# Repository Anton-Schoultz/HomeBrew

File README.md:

# HomeBrew
My attempt at rolling-my-own reto 80's home computer.

Aiming for a 6502 (specifically R65C02) based system,
ideally with video output.

# Tools
Here I have collected the various tools that I needed.
<br>See the README.md in the tools folder for more info.

## EE Programmer
Used to program the EEPROM that I use, the PQ 52B33, which is an 8K rom. 
Programmed via an arduino circuit, using java code on the pc side.

## GAL Programmer
Used to program the GAL20V8s that I use (available and affordable here).
<br>Bassed on the Afterburner project by Bruce Abbott.
<br>I added some convenience batch jobs GAL_Write.bat and GAL_Read.bat.

## Logic Analyser
Here I made use of the excellent PulseView Program,
using a Raspberry Pi Pico as the data capture device.

## WinCUPL
This outdated program from ATMEL is used to compile the fuse info for
programming the GAL20V8 chips.

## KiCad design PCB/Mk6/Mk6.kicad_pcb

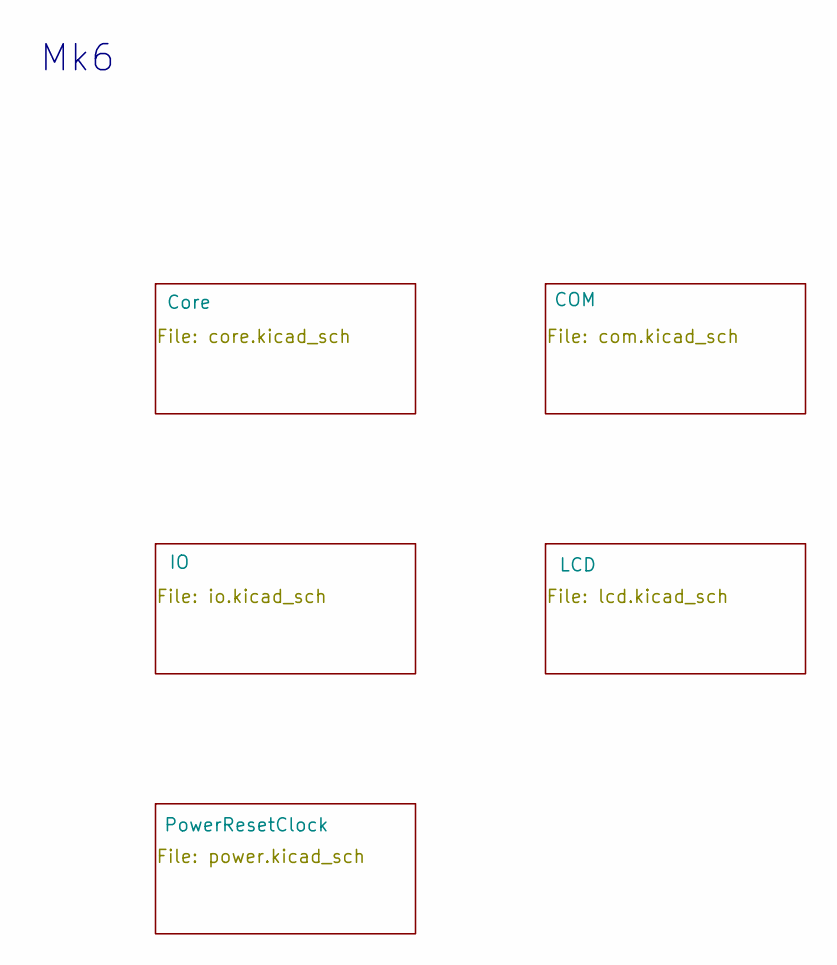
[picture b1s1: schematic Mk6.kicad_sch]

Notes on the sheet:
Mk6

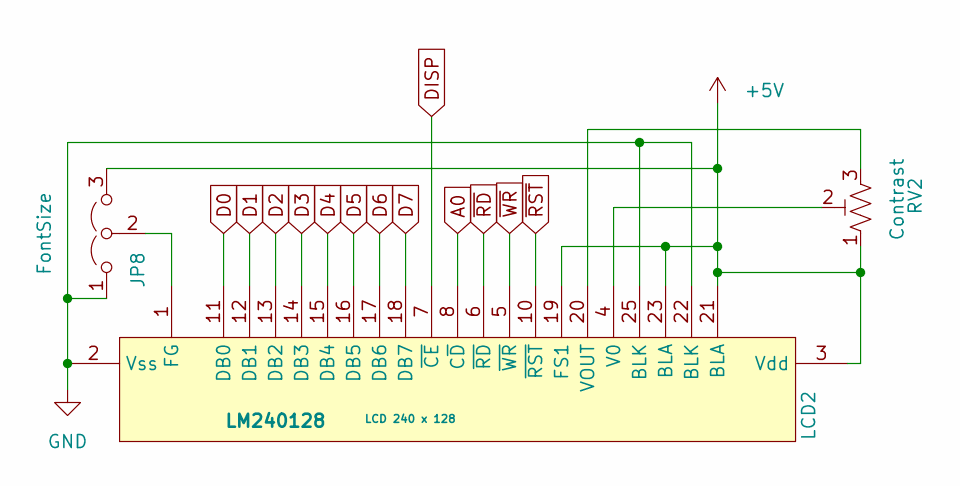
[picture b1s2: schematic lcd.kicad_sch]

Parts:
JP8: FontSize; PinHeader_1x03_P2.54mm_Vertical
LCD2: LM240128; LCD 240x128
RV2: Contrast; Potentiometer_Piher_PT-15-V15_Vertical

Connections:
+5V: JP8.3 (B), LCD2.3 (Vdd), LCD2.19 (FS1), LCD2.21 (BLA), LCD2.23 (BLA), RV2.1; also elsewhere on the board
A0: LCD2.8 (C~D); also elsewhere on the board
D0: LCD2.11 (DB0); also elsewhere on the board
D1: LCD2.12 (DB1); also elsewhere on the board
D2: LCD2.13 (DB2); also elsewhere on the board
D3: LCD2.14 (DB3); also elsewhere on the board
D4: LCD2.15 (DB4); also elsewhere on the board
D5: LCD2.16 (DB5); also elsewhere on the board
D6: LCD2.17 (DB6); also elsewhere on the board
D7: LCD2.18 (DB7); also elsewhere on the board
DISP: LCD2.7 (~CE); also elsewhere on the board
GND: JP8.1 (A), LCD2.2 (Vss), LCD2.22 (BLK), LCD2.25 (BLK); also elsewhere on the board
unnamed: JP8.2 (C), LCD2.1 (FG)
unnamed: LCD2.4 (V0), RV2.2
unnamed: LCD2.20 (VOUT), RV2.3
~RD: LCD2.6 (~RD); also elsewhere on the board
~RST: LCD2.10 (~RST); also elsewhere on the board
~WR: LCD2.5 (~WR); also elsewhere on the board

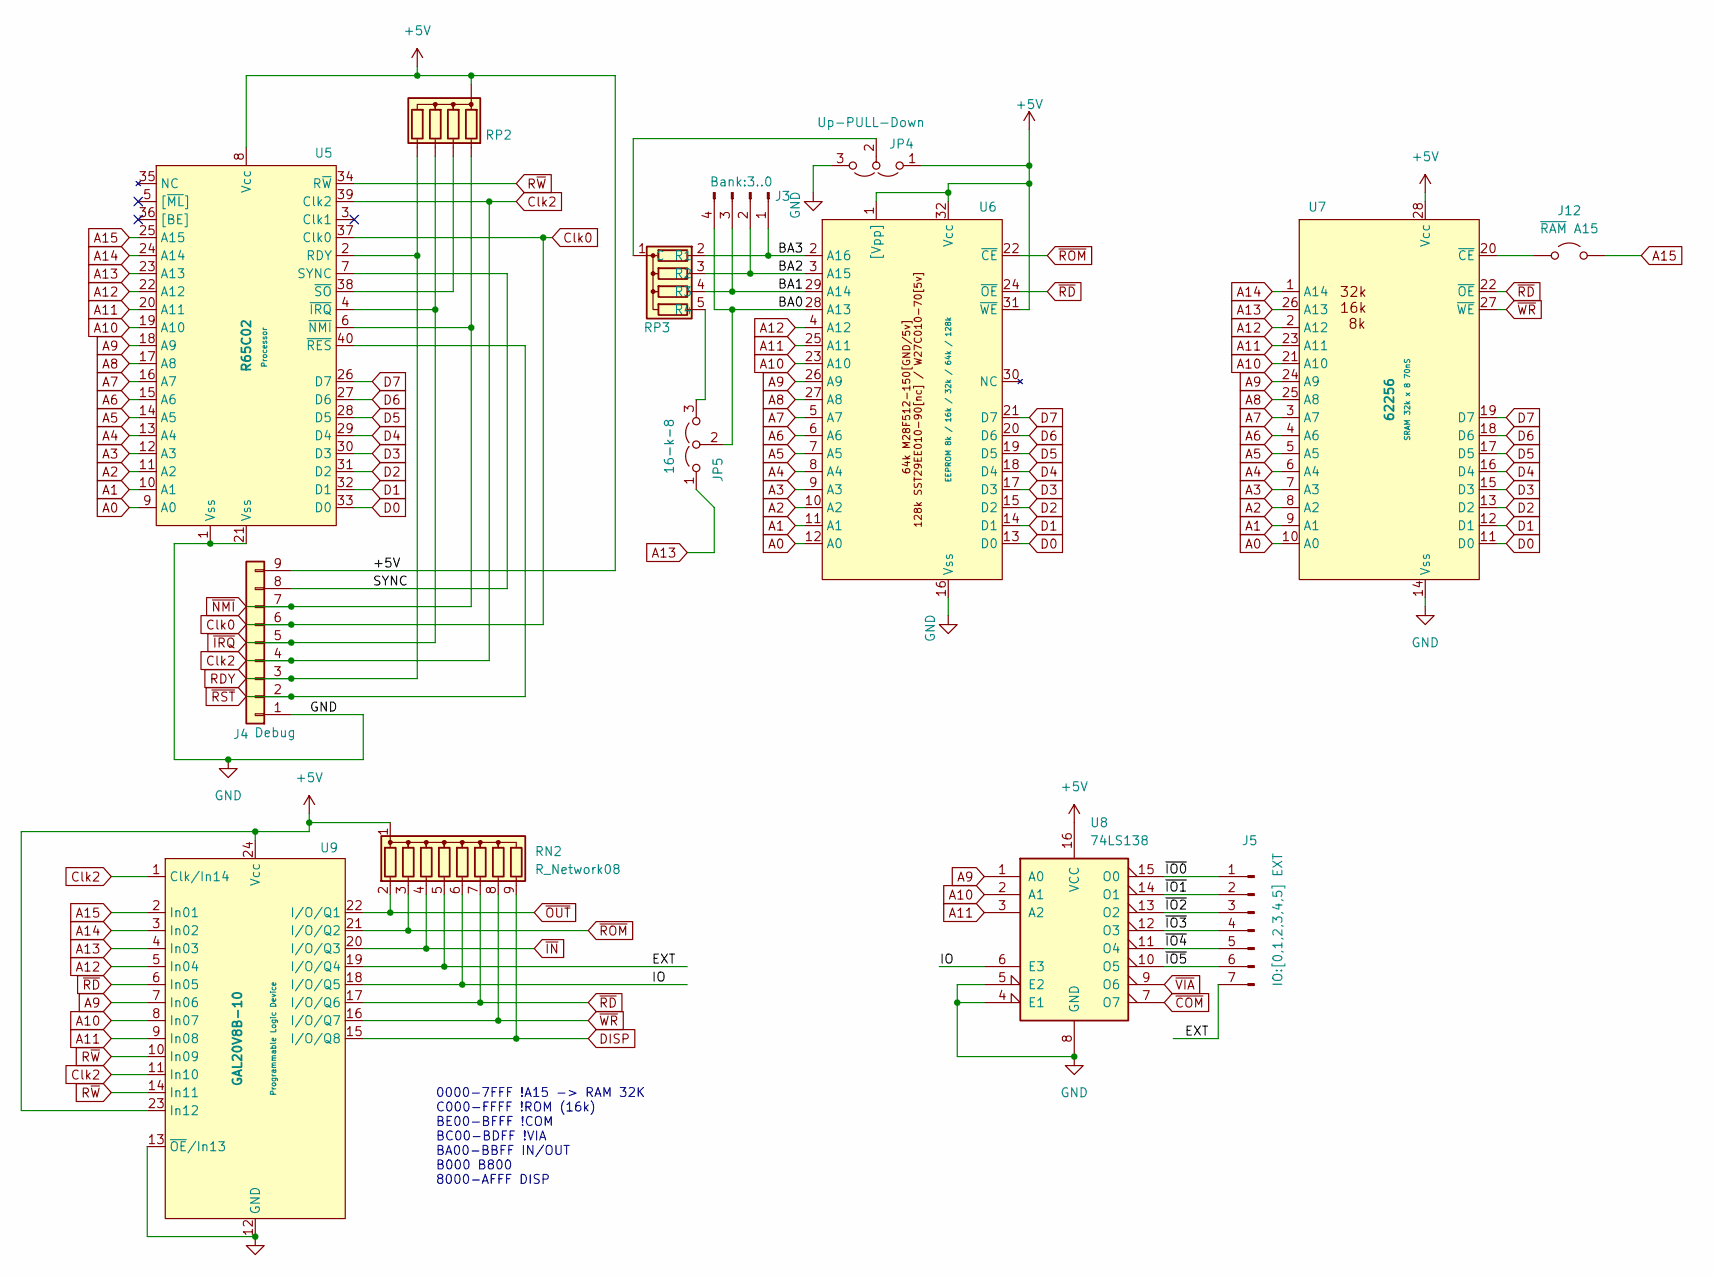
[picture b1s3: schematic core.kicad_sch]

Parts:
J3: Bank:3..0; PinHeader_1x04_P2.54mm_Vertical
J4: Debug; PinHeader_1x09_P2.54mm_Vertical
J5: IO:[0,1,2,3,4,5] EXT; PinSocket_1x07_P2.54mm_Vertical
J12: ~{RAM} A15; PinHeader_1x02_P2.54mm_Vertical
JP4: Up-PULL-Down; PinHeader_1x03_P2.54mm_Vertical
JP5: 16-k-8; PinHeader_1x03_P2.54mm_Vertical
RN2: R_Network08; R_Array_SIP9
RP2, RP3: R_Array_SIP5
U5: R65C02; DIP-40_W15.24mm_LongPads
U6: EEPROM; DIP_Socket-32_W11.9_W12.7_W15.24_W17.78_W18.5_3M_232-1285-0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
U7: 62256; DIP-28_W15.24mm_LongPads
U8: 74LS138; DIP-16_W7.62mm_LongPads
U9: GAL20V8B-10; DIP-24_W7.62mm_LongPads

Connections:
+5V: J4.9, JP4.1 (A), RN2.1 (common), RP2.1 (C), U5.8 (Vcc), U6.1 ([Vpp]), U6.31 (~WE), U6.32 (Vcc), U7.28 (Vcc), U8.16 (VCC), U9.23 (In12), U9.24 (Vcc); also elsewhere on the board
/Core/BA0: J3.4, JP5.2 (C), U6.28 (A13)
/Core/BA1: J3.3, RP3.4 (R3), U6.29 (A14)
/Core/BA2: J3.2, RP3.3 (R2), U6.3 (A15)
/Core/BA3: J3.1, RP3.2 (R1), U6.2 (A16)
/Core/EXT: J5.7, RN2.5 (R4), U9.19 (I/O/Q4)
/Core/IO: RN2.6 (R5), U8.6 (E3), U9.18 (I/O/Q5)
/Core/SYNC: J4.8, U5.7 (SYNC)
/Core/~IO0: J5.1, U8.15 (O0)
/Core/~IO1: J5.2, U8.14 (O1)
/Core/~IO2: J5.3, U8.13 (O2)
/Core/~IO3: J5.4, U8.12 (O3)
/Core/~IO4: J5.5, U8.11 (O4)
/Core/~IO5: J5.6, U8.10 (O5)
A0: U5.9 (A0), U6.12 (A0), U7.10 (A0); also elsewhere on the board
A1: U5.10 (A1), U6.11 (A1), U7.9 (A1); also elsewhere on the board
A2: U5.11 (A2), U6.10 (A2), U7.8 (A2); also elsewhere on the board
A3: U5.12 (A3), U6.9 (A3), U7.7 (A3); also elsewhere on the board
A4: U5.13 (A4), U6.8 (A4), U7.6 (A4); also elsewhere on the board
A5: U5.14 (A5), U6.7 (A5), U7.5 (A5); also elsewhere on the board
A6: U5.15 (A6), U6.6 (A6), U7.4 (A6); also elsewhere on the board
A7: U5.16 (A7), U6.5 (A7), U7.3 (A7); also elsewhere on the board
A8: U5.17 (A8), U6.27 (A8), U7.25 (A8); also elsewhere on the board
A9: U5.18 (A9), U6.26 (A9), U7.24 (A9), U8.1 (A0), U9.7 (In06); also elsewhere on the board
A10: U5.19 (A10), U6.23 (A10), U7.21 (A10), U8.2 (A1), U9.8 (In07); also elsewhere on the board
A11: U5.20 (A11), U6.25 (A11), U7.23 (A11), U8.3 (A2), U9.9 (In08); also elsewhere on the board
A12: U5.22 (A12), U6.4 (A12), U7.2 (A12), U9.5 (In04); also elsewhere on the board
A13: JP5.1 (A), U5.23 (A13), U7.26 (A13), U9.4 (In03)
A14: U5.24 (A14), U7.1 (A14), U9.3 (In02)
A15: J12.2 (B), U5.25 (A15), U9.2 (In01)
Clk0: J4.6, U5.37 (Clk0); also elsewhere on the board
Clk2: J4.4, U5.39 (Clk2), U9.1 (Clk/In14), U9.11 (In10); also elsewhere on the board
D0: U5.33 (D0), U6.13 (D0), U7.11 (D0); also elsewhere on the board
D1: U5.32 (D1), U6.14 (D1), U7.12 (D1); also elsewhere on the board
D2: U5.31 (D2), U6.15 (D2), U7.13 (D2); also elsewhere on the board
D3: U5.30 (D3), U6.17 (D3), U7.15 (D3); also elsewhere on the board
D4: U5.29 (D4), U6.18 (D4), U7.16 (D4); also elsewhere on the board
D5: U5.28 (D5), U6.19 (D5), U7.17 (D5); also elsewhere on the board
D6: U5.27 (D6), U6.20 (D6), U7.18 (D6); also elsewhere on the board
D7: U5.26 (D7), U6.21 (D7), U7.19 (D7); also elsewhere on the board
DISP: RN2.9 (R8), U9.15 (I/O/Q8); also elsewhere on the board
GND: J4.1, JP4.3 (B), U5.1 (Vss), U5.21 (Vss), U6.16 (Vss), U7.14 (Vss), U8.4 (E1), U8.5 (E2), U8.8 (GND), U9.12 (GND), U9.13 (~OE/In13); also elsewhere on the board
unnamed: J12.1 (A), U7.20 (~CE)
unnamed: JP4.2 (C), RP3.1 (C)
unnamed: JP5.3 (B), RP3.5 (R4)
unnamed: RP2.3 (R2), U5.38 (~SO)
RDY: J4.3, RP2.5 (R4), U5.2 (RDY); also elsewhere on the board
R~W: U5.34 (R~W), U9.10 (In09), U9.14 (In11); also elsewhere on the board
~COM: U8.7 (O7); also elsewhere on the board
~IN: RN2.4 (R3), U9.20 (I/O/Q3); also elsewhere on the board
~IRQ: J4.5, RP2.4 (R3), U5.4 (~IRQ); also elsewhere on the board
~NMI: J4.7, RP2.2 (R1), U5.6 (~NMI); also elsewhere on the board
~OUT: RN2.2 (R1), U9.22 (I/O/Q1); also elsewhere on the board
~RD: RN2.7 (R6), U6.24 (~OE), U7.22 (~OE), U9.6 (In05), U9.17 (I/O/Q6); also elsewhere on the board
~ROM: RN2.3 (R2), U6.22 (~CE), U9.21 (I/O/Q2)
~RST: J4.2, U5.40 (~RES); also elsewhere on the board
~VIA: U8.9 (O6); also elsewhere on the board
~WR: RN2.8 (R7), U7.27 (~WE), U9.16 (I/O/Q7); also elsewhere on the board

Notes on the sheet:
0000-7FFF !A15 -> RAM 32K C000-FFFF !ROM (16k) BE00-BFFF !COM BC00-BDFF !VIA BA00-BBFF IN/OUT B000 B800 8000-AFFF DISP

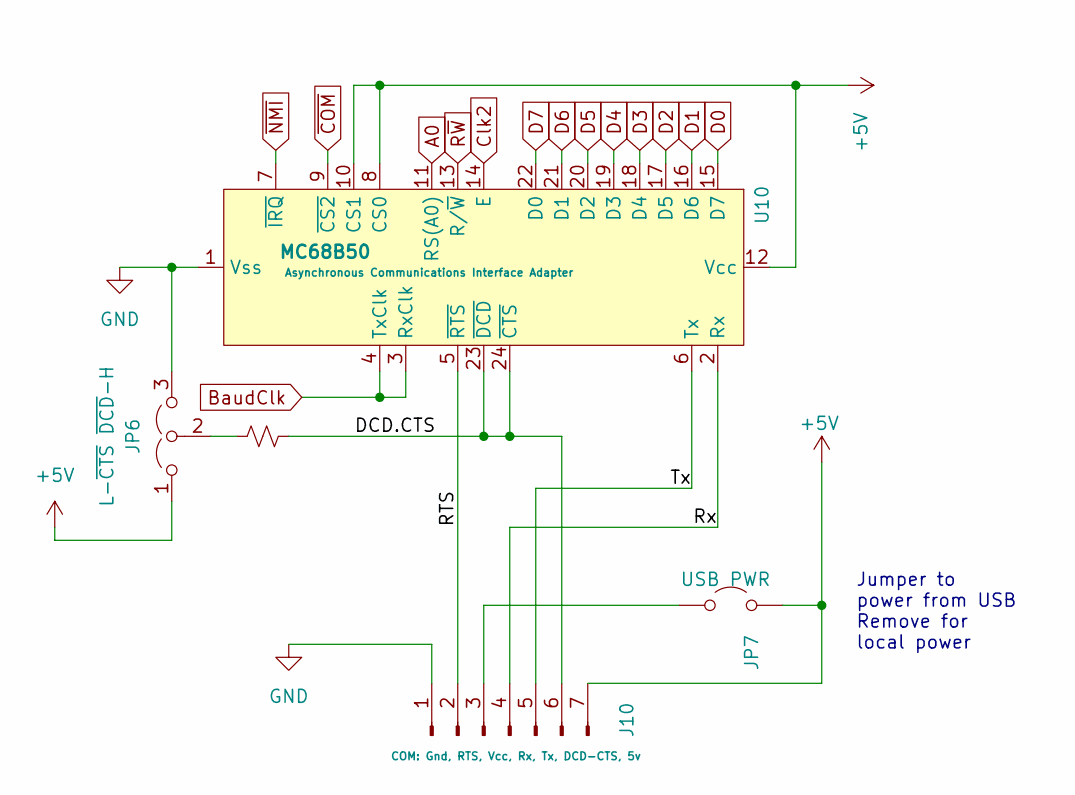
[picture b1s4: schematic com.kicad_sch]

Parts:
J10: COM: Gnd, RTS, Vcc, Rx, Tx, DCD-CTS, 5v; PinSocket_1x07_P2.54mm_Horizontal
JP6: L-~{CTS} ~{DCD}-H; PinHeader_1x03_P2.54mm_Vertical
JP7: USB PWR; PinHeader_1x02_P2.54mm_Vertical
R4: PUp; R_Axial_DIN0204_L3.6mm_D1.6mm_P7.62mm_Horizontal
U10: MC68B50; DIP-24_W15.24mm_LongPads

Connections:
+5V: J10.7, JP6.1 (A), JP7.2 (B), U10.8 (CS0), U10.10 (CS1), U10.12 (Vcc); also elsewhere on the board
/COM/DCD.CTS: J10.6, R4.2, U10.23 (~DCD), U10.24 (~CTS)
/COM/RTS: J10.2, U10.5 (~RTS)
/COM/Rx: J10.4, U10.2 (Rx)
/COM/Tx: J10.5, U10.6 (Tx)
A0: U10.11 (RS(A0)); also elsewhere on the board
BaudClk: U10.3 (RxClk), U10.4 (TxClk); also elsewhere on the board
Clk2: U10.14 (E); also elsewhere on the board
D0: U10.15 (D7); also elsewhere on the board
D1: U10.16 (D6); also elsewhere on the board
D2: U10.17 (D5); also elsewhere on the board
D3: U10.18 (D4); also elsewhere on the board
D4: U10.19 (D3); also elsewhere on the board
D5: U10.20 (D2); also elsewhere on the board
D6: U10.21 (D1); also elsewhere on the board
D7: U10.22 (D0); also elsewhere on the board
GND: J10.1, JP6.3 (B), U10.1 (Vss); also elsewhere on the board
unnamed: J10.3, JP7.1 (A)
unnamed: JP6.2 (C), R4.1
R~W: U10.13 (R/~W); also elsewhere on the board
~COM: U10.9 (~CS2); also elsewhere on the board
~NMI: U10.7 (~IRQ); also elsewhere on the board

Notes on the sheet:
Jumper to power from USB Remove for local power

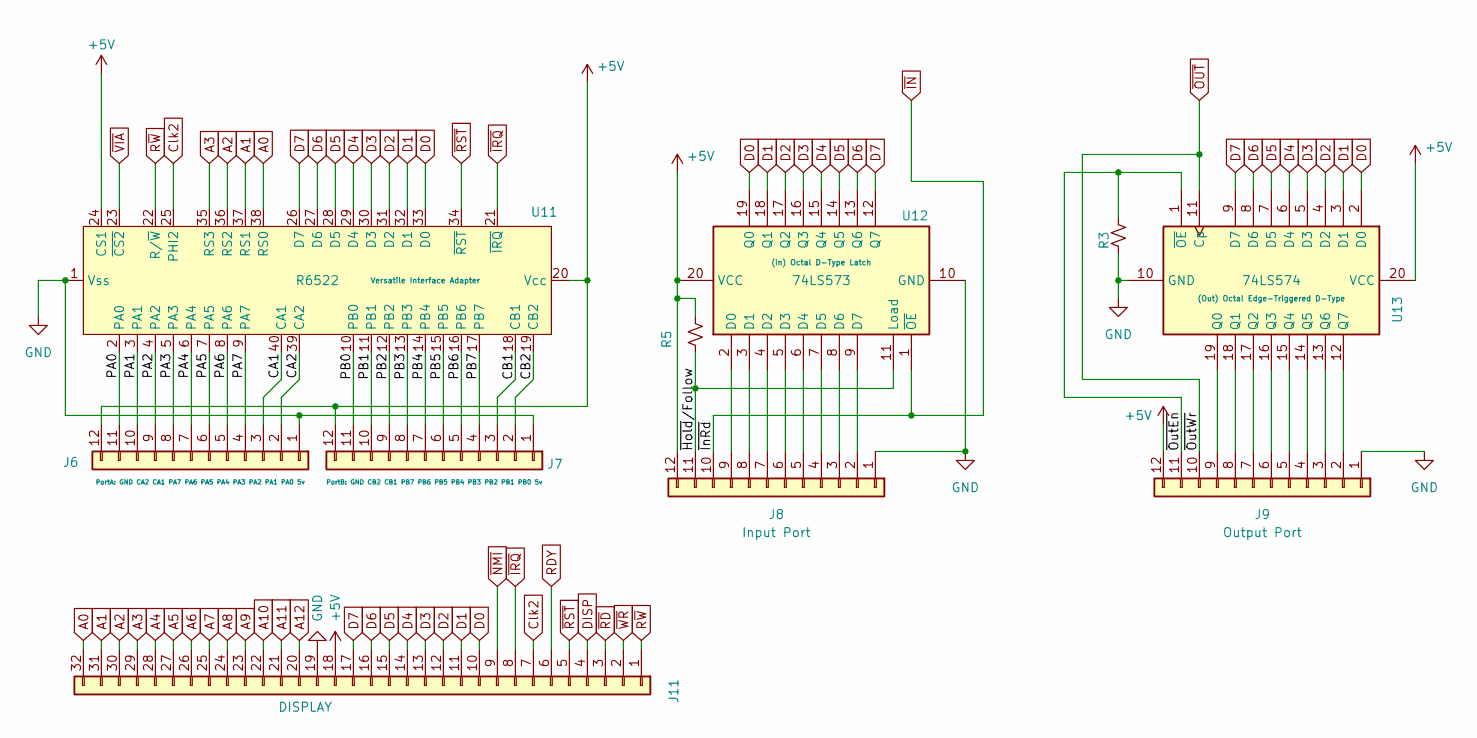
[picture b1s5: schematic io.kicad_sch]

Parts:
J6: PortA: GND CA2 CA1 PA7 PA6 PA5 PA4 PA3 PA2 PA1 PA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; PinSocket_1x12_P2.54mm_Vertical
J7: PortB: GND CB2 CB1 PB7 PB6 PB5 PB4 PB3 PB2 PB1 PB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; PinSocket_1x12_P2.54mm_Vertical
J8: Input Port; PinHeader_1x12_P2.54mm_Vertical
J9: Output Port; PinHeader_1x12_P2.54mm_Vertical
J11: DISPLAY; PinSocket_1x32_P2.54mm_Vertical
R3, R5: R_Small_US; R_Axial_DIN0204_L3.6mm_D1.6mm_P7.62mm_Horizontal
U11: R6522; DIP-40_W15.24mm_LongPads
U12: 74LS573; DIP-20_W7.62mm_LongPads
U13: 74LS574; DIP-20_W7.62mm_LongPads

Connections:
+5V: J6.12, J7.12, J8.12, J9.12, J11.18, R5.1, U11.20 (Vcc), U11.24 (CS1), U12.20 (VCC), U13.20 (VCC); also elsewhere on the board
/IO/CA1: J6.3, U11.40 (CA1)
/IO/CA2: J6.2, U11.39 (CA2)
/IO/CB1: J7.3, U11.18 (CB1)
/IO/CB2: J7.2, U11.19 (CB2)
/IO/PA0: J6.11, U11.2 (PA0)
/IO/PA1: J6.10, U11.3 (PA1)
/IO/PA2: J6.9, U11.4 (PA2)
/IO/PA3: J6.8, U11.5 (PA3)
/IO/PA4: J6.7, U11.6 (PA4)
/IO/PA5: J6.6, U11.7 (PA5)
/IO/PA6: J6.5, U11.8 (PA6)
/IO/PA7: J6.4, U11.9 (PA7)
/IO/PB0: J7.11, U11.10 (PB0)
/IO/PB1: J7.10, U11.11 (PB1)
/IO/PB2: J7.9, U11.12 (PB2)
/IO/PB3: J7.8, U11.13 (PB3)
/IO/PB4: J7.7, U11.14 (PB4)
/IO/PB5: J7.6, U11.15 (PB5)
/IO/PB6: J7.5, U11.16 (PB6)
/IO/PB7: J7.4, U11.17 (PB7)
/IO/~Hold/Follow: J8.11, R5.2, U12.11 (Load)
/IO/~OutEn: J9.11, R3.2, U13.1 (~OE)
A0: J11.32, U11.38 (RS0); also elsewhere on the board
A1: J11.31, U11.37 (RS1); also elsewhere on the board
A2: J11.30, U11.36 (RS2); also elsewhere on the board
A3: J11.29, U11.35 (RS3); also elsewhere on the board
A4: J11.28; also elsewhere on the board
A5: J11.27; also elsewhere on the board
A6: J11.26; also elsewhere on the board
A7: J11.25; also elsewhere on the board
A8: J11.24; also elsewhere on the board
A9: J11.23; also elsewhere on the board
A10: J11.22; also elsewhere on the board
A11: J11.21; also elsewhere on the board
A12: J11.20; also elsewhere on the board
Clk2: J11.7, U11.25 (PHI2); also elsewhere on the board
D0: J11.10, U11.33 (D0), U12.19 (Q0), U13.2 (D0); also elsewhere on the board
D1: J11.11, U11.32 (D1), U12.18 (Q1), U13.3 (D1); also elsewhere on the board
D2: J11.12, U11.31 (D2), U12.17 (Q2), U13.4 (D2); also elsewhere on the board
D3: J11.13, U11.30 (D3), U12.16 (Q3), U13.5 (D3); also elsewhere on the board
D4: J11.14, U11.29 (D4), U12.15 (Q4), U13.6 (D4); also elsewhere on the board
D5: J11.15, U11.28 (D5), U12.14 (Q5), U13.7 (D5); also elsewhere on the board
D6: J11.16, U11.27 (D6), U12.13 (Q6), U13.8 (D6); also elsewhere on the board
D7: J11.17, U11.26 (D7), U12.12 (Q7), U13.9 (D7); also elsewhere on the board
DISP: J11.4; also elsewhere on the board
GND: J6.1, J7.1, J8.1, J9.1, J11.19, R3.1, U11.1 (Vss), U12.10 (GND), U13.10 (GND); also elsewhere on the board
unnamed: J8.2, U12.9 (D7)
unnamed: J8.3, U12.8 (D6)
unnamed: J8.4, U12.7 (D5)
unnamed: J8.5, U12.6 (D4)
unnamed: J8.6, U12.5 (D3)
unnamed: J8.7, U12.4 (D2)
unnamed: J8.8, U12.3 (D1)
unnamed: J8.9, U12.2 (D0)
unnamed: J9.2, U13.12 (Q7)
unnamed: J9.3, U13.13 (Q6)
unnamed: J9.4, U13.14 (Q5)
unnamed: J9.5, U13.15 (Q4)
unnamed: J9.6, U13.16 (Q3)
unnamed: J9.7, U13.17 (Q2)
unnamed: J9.8, U13.18 (Q1)
unnamed: J9.9, U13.19 (Q0)
RDY: J11.6; also elsewhere on the board
R~W: J11.1, U11.22 (R/~W); also elsewhere on the board
~IN: J8.10, U12.1 (~OE); also elsewhere on the board
~IRQ: J11.8, U11.21 (~IRQ); also elsewhere on the board
~NMI: J11.9; also elsewhere on the board
~OUT: J9.10, U13.11 (Cp); also elsewhere on the board
~RD: J11.3; also elsewhere on the board
~RST: J11.5, U11.34 (~RST); also elsewhere on the board
~VIA: U11.23 (~CS2); also elsewhere on the board
~WR: J11.2; also elsewhere on the board

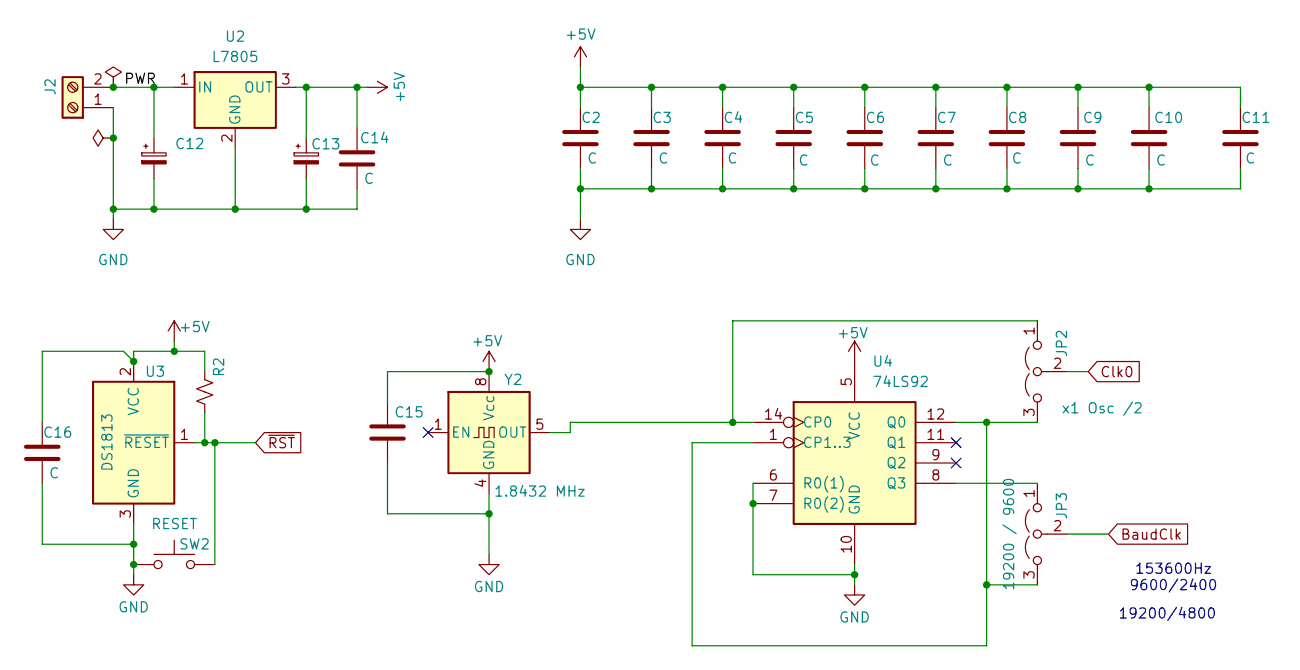
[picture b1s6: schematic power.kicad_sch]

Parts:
C2, C3, C4, C5, C6, C7, C8, C9, C10, C11, C14, C15, C16: C; C_Disc_D7.5mm_W2.5mm_P5.00mm
C12, C13: C_Polarized_Small; CP_Radial_D10.0mm_P7.50mm
J2: Power; TerminalBlock_MaiXu_MX126-5.0-02P_1x02_P5.00mm
JP2: x1 Osc /2; PinHeader_1x03_P2.54mm_Vertical
JP3: 19200 / 9600; PinHeader_1x03_P2.54mm_Vertical
R2: R_Small_US; R_Axial_DIN0204_L3.6mm_D1.6mm_P7.62mm_Horizontal
SW2: RESET; SW_PUSH_1P1T_6x3.5mm_H4.3_APEM_MJTP1243
U2: L7805; TO-220-3_Vertical
U3: DS1813; TO-92L_Wide
U4: 74LS92; DIP-14_W7.62mm_LongPads
Y2: 1.8432 MHz; Oscillator_DIP-8

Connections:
+5V: C2.1, C3.1, C4.1, C5.1, C6.1, C7.1, C8.1, C9.1, C10.1, C11.1, C13.1, C14.1, C15.1, C16.1, R2.1, U2.3 (OUT), U3.2 (VCC), U4.5 (VCC), Y2.8 (Vcc); also elsewhere on the board
/PowerResetClock/PWR: C12.1, J2.2, U2.1 (IN)
BaudClk: JP3.2 (C); also elsewhere on the board
Clk0: JP2.2 (C); also elsewhere on the board
GND: C2.2, C3.2, C4.2, C5.2, C6.2, C7.2, C8.2, C9.2, C10.2, C11.2, C12.2, C13.2, C14.2, C15.2, C16.2, J2.1, SW2.1, U2.2 (GND), U3.3 (GND), U4.6 (R0(1)), U4.7 (R0(2)), U4.10 (GND), Y2.4 (GND); also elsewhere on the board
unnamed: JP2.1 (A), U4.14 (CP0), Y2.5 (OUT)
unnamed: JP2.3 (B), JP3.3 (B), U4.1 (CP1..3), U4.12 (Q0)
unnamed: JP3.1 (A), U4.8 (Q3)
~RST: R2.2, SW2.2, U3.1 (~RESET); also elsewhere on the board

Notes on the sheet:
153600Hz 9600/2400
19200/4800

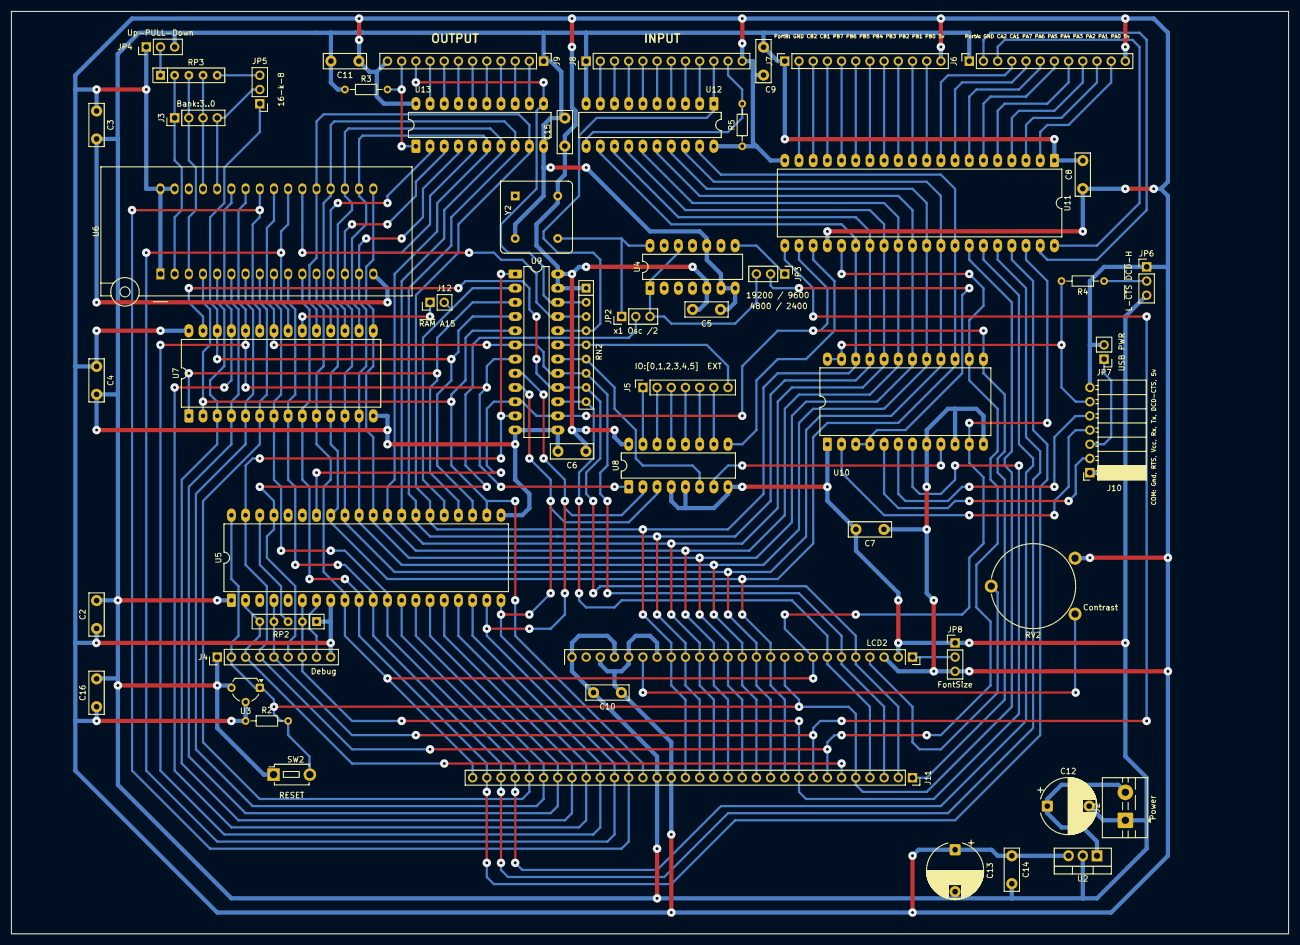
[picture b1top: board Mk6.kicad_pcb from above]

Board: 2 copper layers, 228.6 x 165.1 mm, 56 parts (0 on the bottom side), 110 nets.

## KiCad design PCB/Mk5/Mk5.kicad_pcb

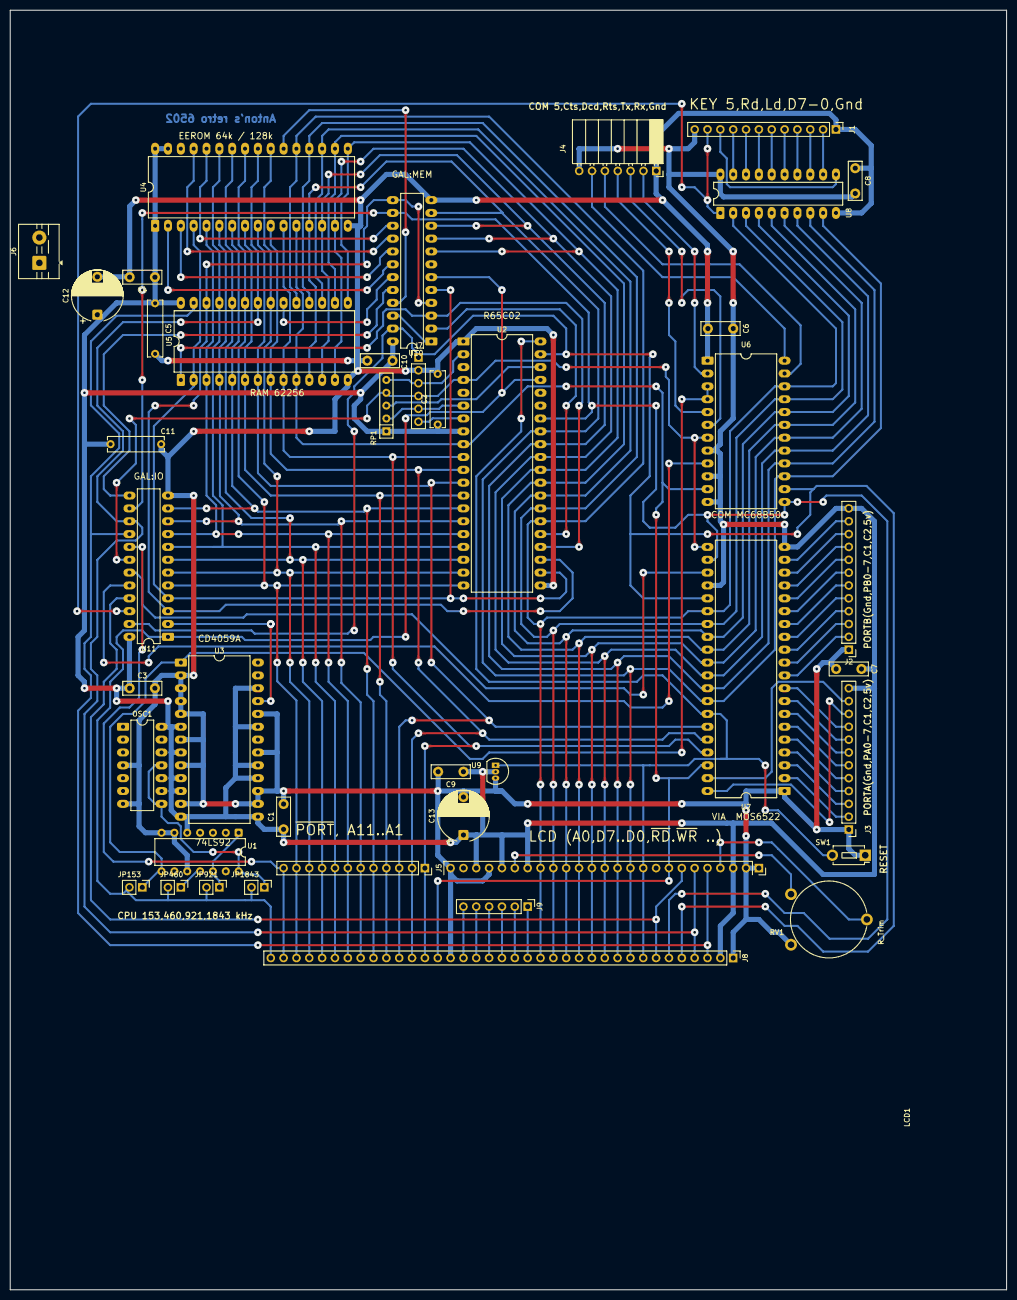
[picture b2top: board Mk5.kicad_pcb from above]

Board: 2 copper layers, 197.0 x 253.0 mm, 42 parts (0 on the bottom side), 97 nets.

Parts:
C1, C3, C4, C6, C7, C8, C9, C10: C; C_Disc_D7.5mm_W2.5mm_P5.00mm
C2, C5, C11: C; C_Rect_L11.0mm_W2.8mm_P10.00mm_MKT
C12, C13: C_Polarized_Small; CP_Radial_D10.0mm_P7.50mm
J1: KeyBoard 5,Rd,Ld,D7..0,Gnd; PinHeader_1x12_P2.54mm_Vertical
J2: PortB; PinHeader_1x12_P2.54mm_Vertical
J3: PortA; PinHeader_1x12_P2.54mm_Vertical
J4: COM: Gnd,Rx,Tx,Rts,Dcd,Cts,5v; PinSocket_1x07_P2.54mm_Horizontal
J5: Conn_01x12; PinSocket_1x12_P2.54mm_Vertical
J6: Screw_Terminal_01x02; TerminalBlock_MaiXu_MX126-5.0-02P_1x02_P5.00mm
J7, J9: Conn_01x06_Pin; PinHeader_1x06_P2.54mm_Vertical
J8: Conn_01x37_Pin; PinHeader_1x37_P2.54mm_Vertical
JP153, JP460, JP921, JP1843: Jumper_2_Open; PinHeader_1x02_P2.54mm_Vertical
LCD1: LM240128; LCD 240x128
OSC1: DIP-14_W7.62mm_LongPads
RP1: R_Array_SIP5
RV1: R_Trim; Potentiometer_Piher_PT-15-V15_Vertical
SW1: RST; SW_PUSH_1P1T_6x3.5mm_H4.3_APEM_MJTP1243
U1: 74LS92; DIP-14_W7.62mm
U2: R65C02; DIP-40_W15.24mm_LongPads
U3: CD4059A; DIP-26_W15.24mm_LongPads
U4: EEPROM; DIP-32_W15.24mm_LongPads
U5: 62256; DIP-28_W15.24mm_LongPads
U6: MC68B50; DIP-24_W15.24mm_LongPads
U7: R6522; DIP-40_W15.24mm_LongPads
U8: 74LS573; DIP-20_W7.62mm_LongPads
U9: DS1813; TO-92L_Inline
U10, U11: GAL20V8B-10; DIP-24_W7.62mm_LongPads

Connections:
+5V: C1.1, C2.1, C3.1, C4.1, C5.1, C6.1, C7.1, C8.1, C9.1, C10.1, C11.1, C12.1, C13.1, J1.12, J2.12, J3.12, J4.7, J6.2, J8.2, LCD1.3 (Vdd), LCD1.19 (FS1), LCD1.21 (BLA), LCD1.23 (BLA), OSC1.14 (Vcc), RP1.1 (C), U1.5 (VCC), U2.8 (Vcc), U3.6 (R8.J4), U3.8 (J15.H4), U3.10 (J13.H1), U3.11 (Kc), U3.13 (Kb), U3.14 (Ka), U3.17 (J10.T2), U3.18 (J09.T1), U3.20 (J07.U4), U3.21 (J06.U2), U3.24 (Vcc), U4.1 ([Vpp]), U4.31 (~WE), U4.32 (Vcc), U5.28 (Vcc), U6.8 (CS0), U6.10 (CS1), U6.12 (Vcc), U7.20 (Vcc), U7.24 (CS1), U8.20 (VCC), U9.2 (VCC), U10.24 (Vcc), U11.24 (Vcc)
/A0: J8.24, LCD1.8 (C~D), U2.9 (A0), U4.12 (A0), U5.10 (A0), U6.11 (RS(A0)), U7.38 (RS0)
/A1: J5.1, J8.25, U2.10 (A1), U4.11 (A1), U5.9 (A1), U7.37 (RS1)
/A2: J5.2, J8.26, U2.11 (A2), U4.10 (A2), U5.8 (A2), U7.36 (RS2)
/A3: J5.3, J8.27, U2.12 (A3), U4.9 (A3), U5.7 (A3), U7.35 (RS3)
/A4: J5.4, J8.28, U2.13 (A4), U4.8 (A4), U5.6 (A4)
/A5: J5.5, J8.29, U2.14 (A5), U4.7 (A5), U5.5 (A5), U11.11 (In10)
/A6: J5.6, J8.30, U2.15 (A6), U4.6 (A6), U5.4 (A6), U11.10 (In09)
/A7: J5.7, J8.31, U2.16 (A7), U4.5 (A7), U5.3 (A7), U11.9 (In08)
/A8: J5.8, J8.32, U2.17 (A8), U4.27 (A8), U5.25 (A8), U11.8 (In07)
/A9: J5.9, J8.33, U2.18 (A9), U4.26 (A9), U5.24 (A9), U11.7 (In06)
/A10: J5.10, J8.34, U2.19 (A10), U4.23 (A10), U5.21 (A10), U11.6 (In05)
/A11: J5.11, J8.35, U2.20 (A11), U4.25 (A11), U5.23 (A11), U11.5 (In04)
/A12: U2.22 (A12), U4.4 (A12), U5.2 (A12), U10.5 (In04), U11.4 (In03)
/A13: U2.23 (A13), U5.26 (A13), U10.4 (In03), U10.13 (~OE/In13), U11.3 (In02)
/A14: U2.24 (A14), U5.1 (A14), U10.3 (In02)
/A15: U2.25 (A15), U10.2 (In01)
/BA0: U4.28 (A13), U10.15 (I/O/Q8)
/BA1: U4.29 (A14), U10.16 (I/O/Q7)
/BA2: U4.3 (A15), U10.17 (I/O/Q6)
/BA3: U4.2 (A16), U10.18 (I/O/Q5)
/BankWr: U10.1 (Clk/In14), U10.22 (I/O/Q1)
/BaudClk: JP153.1 (A), U1.8 (Q3), U3.1 (CLK), U6.3 (RxClk), U6.4 (TxClk)
/Clk0: J8.37, JP153.2 (B), JP460.2 (B), JP921.2 (B), JP1843.2 (B), U2.37 (Clk0), U10.6 (In05), U11.1 (Clk/In14)
/Clk2: J7.1, J8.5, U2.39 (Clk2), U6.14 (E), U7.25 (PHI2), U10.23 (In12), U11.23 (In12)
/D0: J8.9, LCD1.11 (DB0), U2.33 (D0), U4.13 (D0), U5.11 (D0), U6.15 (D7), U7.33 (D0), U8.9 (D7), U10.11 (In10)
/D1: J8.10, LCD1.12 (DB1), U2.32 (D1), U4.14 (D1), U5.12 (D1), U6.16 (D6), U7.32 (D1), U8.8 (D6), U10.10 (In09)
/D2: J8.11, LCD1.13 (DB2), U2.31 (D2), U4.15 (D2), U5.13 (D2), U6.17 (D5), U7.31 (D2), U8.7 (D5), U10.9 (In08)
/D3: J8.12, LCD1.14 (DB3), U2.30 (D3), U4.17 (D3), U5.15 (D3), U6.18 (D4), U7.30 (D3), U8.6 (D4), U10.8 (In07)
/D4: J8.13, LCD1.15 (DB4), U2.29 (D4), U4.18 (D4), U5.16 (D4), U6.19 (D3), U7.29 (D4), U8.5 (D3)
/D5: J8.14, LCD1.16 (DB5), U2.28 (D5), U4.19 (D5), U5.17 (D5), U6.20 (D2), U7.28 (D5), U8.4 (D2)
/D6: J8.15, LCD1.17 (DB6), U2.27 (D6), U4.20 (D6), U5.18 (D6), U6.21 (D1), U7.27 (D6), U8.3 (D1)
/D7: J8.16, LCD1.18 (DB7), U2.26 (D7), U4.21 (D7), U5.19 (D7), U6.22 (D0), U7.26 (D7), U8.2 (D0)
/DISP: J8.7, LCD1.7 (~CE), U11.21 (I/O/Q2)
/LD: J1.10, U8.11 (Load)
/Q0: J8.17, J9.1
/Q1: J8.18, J9.2
/Q2: J8.19, J9.3
/Q3: J8.20, J9.4
/Q4: J8.21, J9.5
/Q5: J8.22, J9.6
/RDY: J7.3, RP1.5 (R4), U2.2 (RDY)
/R~W: J8.6, U2.34 (R~W), U6.13 (R/~W), U7.22 (R/~W), U10.14 (In11), U11.14 (In11)
/SYNC: J7.6, U2.7 (SYNC)
/TMR: U3.23 (OUT), U11.2 (In01)
/~COM: U6.9 (~CS2), U11.20 (I/O/Q3)
/~IO: U10.20 (I/O/Q3), U11.13 (~OE/In13)
/~IRQ: J7.4, RP1.4 (R3), U2.4 (~IRQ), U6.7 (~IRQ), U7.21 (~IRQ), U11.18 (I/O/Q5)
/~KEY: J1.11, U8.1 (~OE), U11.22 (I/O/Q1)
/~NMI: J7.5, RP1.2 (R1), U2.6 (~NMI)
/~PORT: J5.12, J8.36, U11.17 (I/O/Q6)
/~RAM: U5.20 (~CE), U10.19 (I/O/Q4)
/~RD: J8.4, LCD1.6 (~RD), U4.24 (~OE), U5.22 (~OE), U11.15 (I/O/Q8)
/~ROM: U4.22 (~CE), U10.21 (I/O/Q2)
/~RST: J8.8, LCD1.10 (~RST), SW1.2, U2.40 (~RES), U7.34 (~RST), U9.1 (~RESET)
/~SO: RP1.3 (R2), U2.38 (~SO)
/~VIA: U7.23 (~CS2), U11.19 (I/O/Q4)
/~WR: J8.3, LCD1.5 (~WR), U5.27 (~WE), U11.16 (I/O/Q7)
GND: C1.2, C2.2, C3.2, C4.2, C5.2, C6.2, C7.2, C8.2, C9.2, C10.2, C11.2, C12.2, C13.2, J1.1, J2.1, J3.1, J4.1, J6.1, J7.2, J8.1, J8.23, LCD1.1 (FG), LCD1.2 (Vss), LCD1.22 (BLK), LCD1.25 (BLK), OSC1.4 (GND), OSC1.7 (GND), RV1.1, SW1.1, U1.6 (R0(1)), U1.7 (R0(2)), U1.10 (GND), U2.1 (Vss), U2.21 (Vss), U3.2 (LE), U3.3 (R1.J1), U3.4 (R2.J2), U3.5 (R4.J3), U3.7 (J16.H8), U3.9 (J14.H2), U3.12 (Vss), U3.15 (J12.T8), U3.16 (J11.T4), U3.19 (J08.U8), U3.22 (J05.U1), U4.16 (Vss), U5.14 (Vss), U6.1 (Vss), U7.1 (Vss), U8.10 (GND), U9.3 (GND), U10.12 (GND), U11.12 (GND)
unnamed: J1.2, U8.12 (Q7)
unnamed: J1.3, U8.13 (Q6)
unnamed: J1.4, U8.14 (Q5)
unnamed: J1.5, U8.15 (Q4)
unnamed: J1.6, U8.16 (Q3)
unnamed: J1.7, U8.17 (Q2)
unnamed: J1.8, U8.18 (Q1)
unnamed: J1.9, U8.19 (Q0)
unnamed: J2.2, U7.10 (PB0)
unnamed: J2.3, U7.11 (PB1)
unnamed: J2.4, U7.12 (PB2)
unnamed: J2.5, U7.13 (PB3)
unnamed: J2.6, U7.14 (PB4)
unnamed: J2.7, U7.15 (PB5)
unnamed: J2.8, U7.16 (PB6)
unnamed: J2.9, U7.17 (PB7)
unnamed: J2.10, U7.18 (CB1)
unnamed: J2.11, U7.19 (CB2)
unnamed: J3.2, U7.2 (PA0)
unnamed: J3.3, U7.3 (PA1)
unnamed: J3.4, U7.4 (PA2)
unnamed: J3.5, U7.5 (PA3)
unnamed: J3.6, U7.6 (PA4)
unnamed: J3.7, U7.7 (PA5)
unnamed: J3.8, U7.8 (PA6)
unnamed: J3.9, U7.9 (PA7)
unnamed: J3.10, U7.40 (CA1)
unnamed: J3.11, U7.39 (CA2)
unnamed: J4.2, U6.2 (Rx)
unnamed: J4.3, U6.6 (Tx)
unnamed: J4.4, U6.5 (~RTS)
unnamed: J4.5, U6.23 (~DCD)
unnamed: J4.6, U6.24 (~CTS)
unnamed: JP460.1 (A), U1.11 (Q1)
unnamed: JP921.1 (A), U1.1 (CP1..3), U1.12 (Q0)
unnamed: JP1843.1 (A), OSC1.8 (OUT), OSC1.11 (OUT), U1.14 (CP0)
unnamed: LCD1.4 (V0), RV1.2
unnamed: LCD1.20 (VOUT), RV1.3
